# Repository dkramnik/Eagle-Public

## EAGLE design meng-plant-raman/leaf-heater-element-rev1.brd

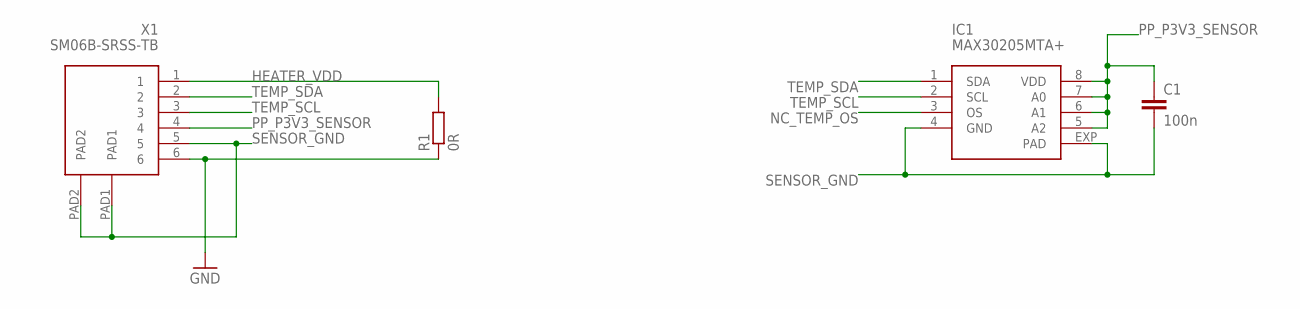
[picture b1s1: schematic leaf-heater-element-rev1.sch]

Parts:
C1: 100n; C0402
IC1: MAX30205MTA+; TDFN-08
R1: 0R; R0603
X1: SM06B-SRSS-TB; JST-SM06B-SRSS-TB

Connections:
GND: R1.1, X1.6
HEATER_VDD: R1.2, X1.1
NC_TEMP_OS: IC1.3 (OS)
PP_P3V3_SENSOR: C1.1, IC1.5 (A2), IC1.6 (A1), IC1.7 (A0), IC1.8 (VDD), X1.4
SENSOR_GND: C1.2, IC1.4 (GND), IC1.EXP (PAD), X1.5, X1.PAD1, X1.PAD2
TEMP_SCL: IC1.2 (SCL), X1.3
TEMP_SDA: IC1.1 (SDA), X1.2

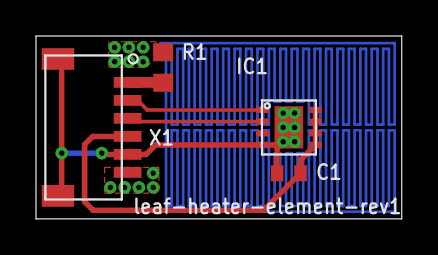
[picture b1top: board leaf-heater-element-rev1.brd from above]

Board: 2 copper layers, 20.3 x 10.2 mm, 4 parts (0 on the bottom side), 6 nets.

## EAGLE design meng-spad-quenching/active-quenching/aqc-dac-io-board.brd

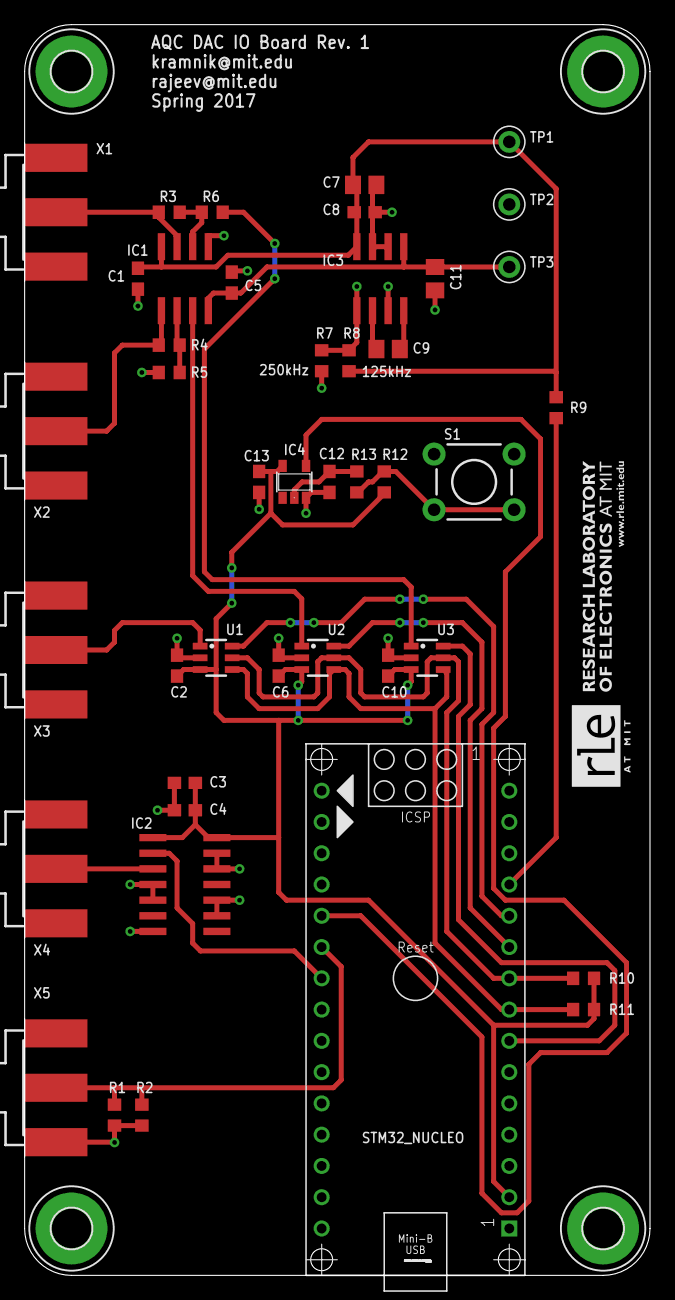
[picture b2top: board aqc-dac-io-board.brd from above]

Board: 2 copper layers, 50.8 x 101.6 mm, 47 parts (0 on the bottom side), 26 nets.

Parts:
C1, C2, C3, C5, C6, C8, C10, C12, C13: 100n; C0603
C4: 10n; C0603
C7, C9, C11: 4u7; C0805
H1, H2, H3, H4: MOUNT-PAD-ROUND3.2; 3,2-PAD
IC1: LT1366; SO08
IC2: 74LVT126; SO14
IC3: MAX1680; SO8
IC4: 74AHC1G14DBV; SOT23-5
R1, R2: 100R; R0603
R3: 15k0; R0603
R4: 5k11; R0603
R5, R6: 10k0; R0603
R7, R9: 0R; R0603
R8: DNP; R0603
R10, R11: 2k2; R0603
R12: 4k7; R0603
R13: 100k; R0603
S1: TACTILE-PTH
STM32_NUCLEO: ARDUINO_NANO
TP1: PP_P5V0; KEYSTONE_5000_MINIATURE
TP2: GND; KEYSTONE_5000_MINIATURE
TP3: PP_N5V0; KEYSTONE_5000_MINIATURE
U1, U2, U3: MCP4725; SOT23-6
X1: CONN_VREF_CASCODE_IBIAS; J502-ND-142-0701-801/806
X2: CONN_VREF_DIAMOND_IBIAS; J502-ND-142-0701-801/806
X3: CONN_VREF_ONE_SHOT; J502-ND-142-0701-801/806
X4: CONN_FORCE_QUENCH; J502-ND-142-0701-801/806
X5: CONN_PHOTON_COUNTER; J502-ND-142-0701-801/806

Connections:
DAC_CASCODE_IBIAS_SEL: STM32_NUCLEO.7, U3.6
DAC_DIAMOND_IBIAS_SEL: STM32_NUCLEO.10, U2.6
DAC_ONE_SHOT_SEL: STM32_NUCLEO.11, U1.6
DAC_SCL: R10.1, STM32_NUCLEO.9, U1.5, U2.5, U3.5
DAC_SDA: R11.1, STM32_NUCLEO.8, U1.4, U2.4, U3.4
FORCE_QUENCH_BUF: IC2.3, X4.1
FORCE_QUENCH_MCU: IC2.2, STM32_NUCLEO.22
GND: C1.2, C2.2, C3.2, C4.2, C5.2, C6.2, C7.2, C8.2, C10.2, C11.2, C12.2, C13.2, H1.B3,2, H2.B3,2, H3.B3,2, H4.B3,2, IC1.5, IC2.4, IC2.5, IC2.7, IC2.9, IC2.10, IC2.12, IC2.13, IC3.3, IC3.6, IC3.7, IC4.3, R1.1, R2.1, R5.1, R7.1, S1.1, S1.2, STM32_NUCLEO.14, STM32_NUCLEO.19, TP2.P$1, U1.2, U2.2, U3.2, X1.G@1, X1.G@2, X1.G@3, X1.G@4, X2.G@1, X2.G@2, X2.G@3, X2.G@4, X3.G@1, X3.G@2, X3.G@3, X3.G@4, X4.G@1, X4.G@2, X4.G@3, X4.G@4, X5.G@1, X5.G@2, X5.G@3, X5.G@4
unnamed: U1.1, X3.1
unnamed: R6.2, U3.1
unnamed: IC1.6, R3.2, R6.1
unnamed: IC3.1, R7.2, R8.1
unnamed: IC1.7, R3.1, X1.1
unnamed: IC1.3, U2.1
unnamed: IC1.1, R4.2, X2.1
unnamed: IC1.2, R4.1, R5.2
unnamed: R9.2, STM32_NUCLEO.12
unnamed: R12.1, R13.2, S1.3, S1.4
unnamed: C12.1, IC4.2, R13.1
unnamed: C9.2, IC3.4
unnamed: C9.1, IC3.2
PHOTON_COUNTER: R1.2, R2.2, STM32_NUCLEO.21, X5.1
PP_N5V0: C5.1, C11.1, IC1.4, IC3.5, TP3.P$1
PP_P3V3: C2.1, C3.1, C4.1, C6.1, C10.1, C13.1, IC2.1, IC2.14, IC4.5, R10.2, R11.2, R12.2, STM32_NUCLEO.2, U1.3, U2.3, U3.3
PP_P5V0: C1.1, C7.1, C8.1, IC1.8, IC3.8, R8.2, R9.1, TP1.P$1
TRIGGER_BTN: IC4.4, STM32_NUCLEO.20

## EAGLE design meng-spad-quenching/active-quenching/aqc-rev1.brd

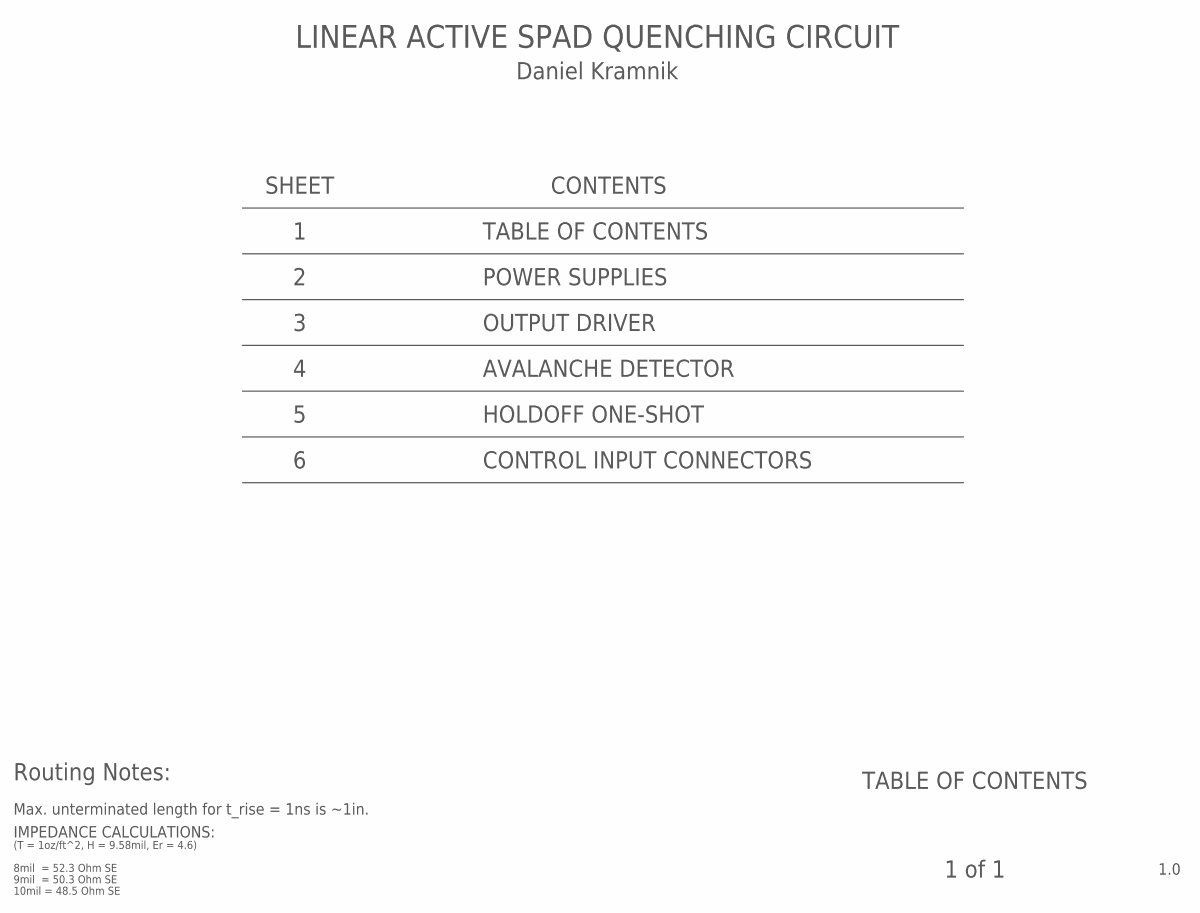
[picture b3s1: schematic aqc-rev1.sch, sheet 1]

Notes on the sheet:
IMPEDANCE CALCULATIONS:
(T = 1oz/ft^2, H = 9.58mil, Er = 4.6)
9mil = 50.3 Ohm SE
10mil = 48.5 Ohm SE
8mil = 52.3 Ohm SE
TABLE OF CONTENTS
1.0
1 of 1
LINEAR ACTIVE SPAD QUENCHING CIRCUIT
SHEET
CONTENTS
Daniel Kramnik
POWER SUPPLIES
OUTPUT DRIVER
AVALANCHE DETECTOR
HOLDOFF ONE-SHOT
CONTROL INPUT CONNECTORS
Routing Notes:
Max. unterminated length for t_rise = 1ns is ~1in.

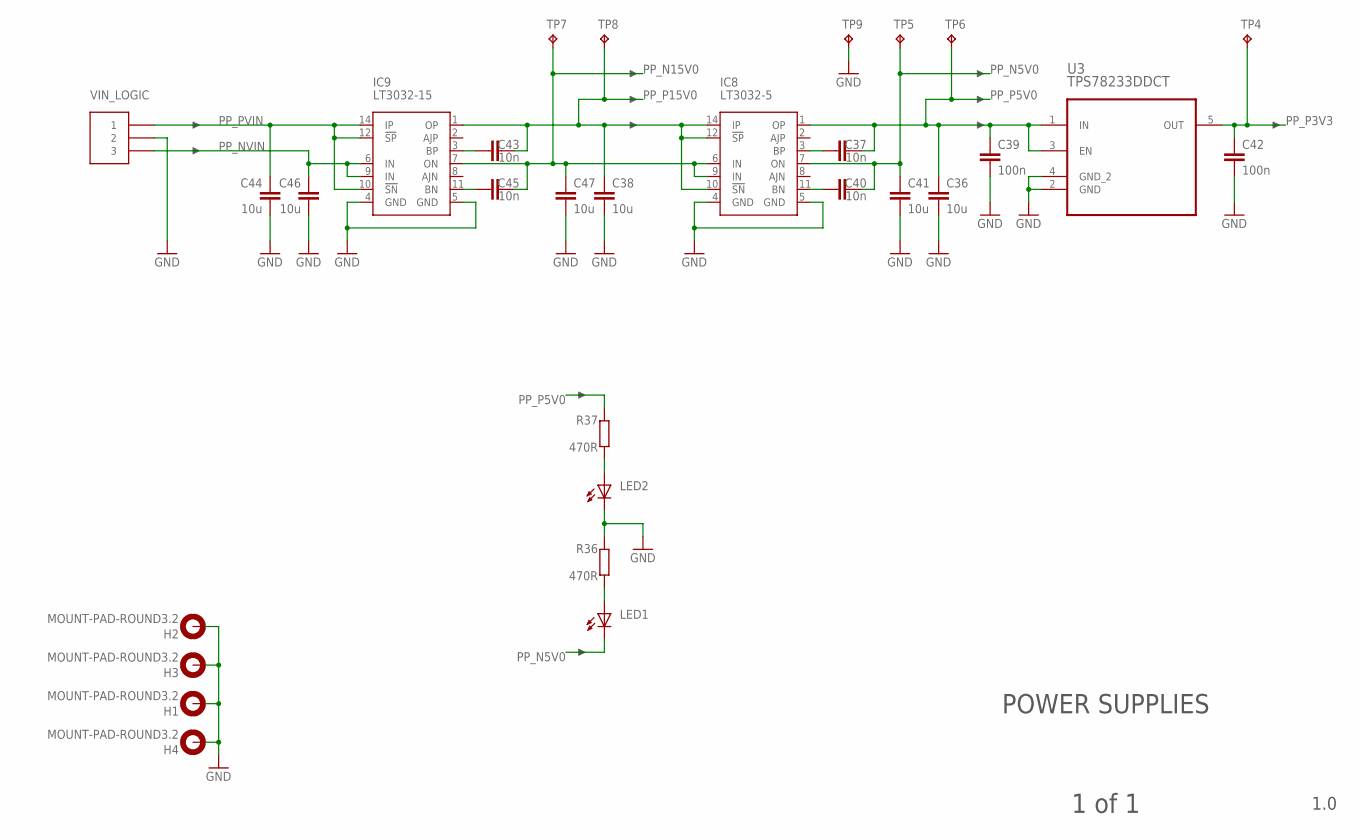
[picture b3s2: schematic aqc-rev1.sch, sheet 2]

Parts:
C36, C38, C41, C44, C46, C47: 10u; C1206
C37, C40, C43, C45: 10n; C0603
C39, C42: 100n; C0603
H1, H2, H3, H4: MOUNT-PAD-ROUND3.2; 3,2-PAD
IC8: LT3032-5; DFN14-4X3DE
IC9: LT3032-15; DFN14-4X3DE
J1: VIN_LOGIC; CONN_MOLEX_3PIN_MINI-FIT_JR
LED1, LED2: LEDCHIP-LED0805; CHIP-LED0805
R36, R37: 470R; R0805
TP4, TP5, TP6, TP7, TP8, TP9: TPTP20R; TP20R
U3: TPS78233DDCT; SOT95P280X110-5N

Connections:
GND: C36.2, C38.2, C39.2, C41.2, C42.2, C44.2, C46.2, C47.2, H1.B3,2, H2.B3,2, H3.B3,2, H4.B3,2, IC8.4 (GND), IC8.5 (GND), IC9.4 (GND), IC9.5 (GND), J1.2, LED2.C, R36.2, TP9.TP, U3.2 (GND), U3.4 (GND_2); also elsewhere on the board
unnamed: C37.1, IC8.3 (BP)
unnamed: C40.1, IC8.11 (BN)
unnamed: C43.1, IC9.3 (BP)
unnamed: C45.1, IC9.11 (BN)
unnamed: LED1.A, R36.1
unnamed: LED2.A, R37.1
PP_N5V0: C40.2, C41.1, IC8.7 (ON), LED1.C, TP5.TP; also elsewhere on the board
PP_N15V0: C45.2, C47.1, IC8.6 (IN), IC8.9 (IN), IC9.7 (ON), TP7.TP
PP_NVIN: C46.1, IC9.6 (IN), IC9.9 (IN), J1.3
PP_P3V3: C42.1, TP4.TP, U3.5 (OUT); also elsewhere on the board
PP_P5V0: C36.1, C37.2, C39.1, IC8.1 (OP), R37.2, TP6.TP, U3.1 (IN), U3.3 (EN); also elsewhere on the board
PP_P15V0: C38.1, C43.2, IC8.10 (!SN), IC8.12 (!SP), IC8.14 (IP), IC9.1 (OP), TP8.TP; also elsewhere on the board
PP_PVIN: C44.1, IC9.10 (!SN), IC9.12 (!SP), IC9.14 (IP), J1.1

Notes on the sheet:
POWER SUPPLIES
1.0
1 of 1

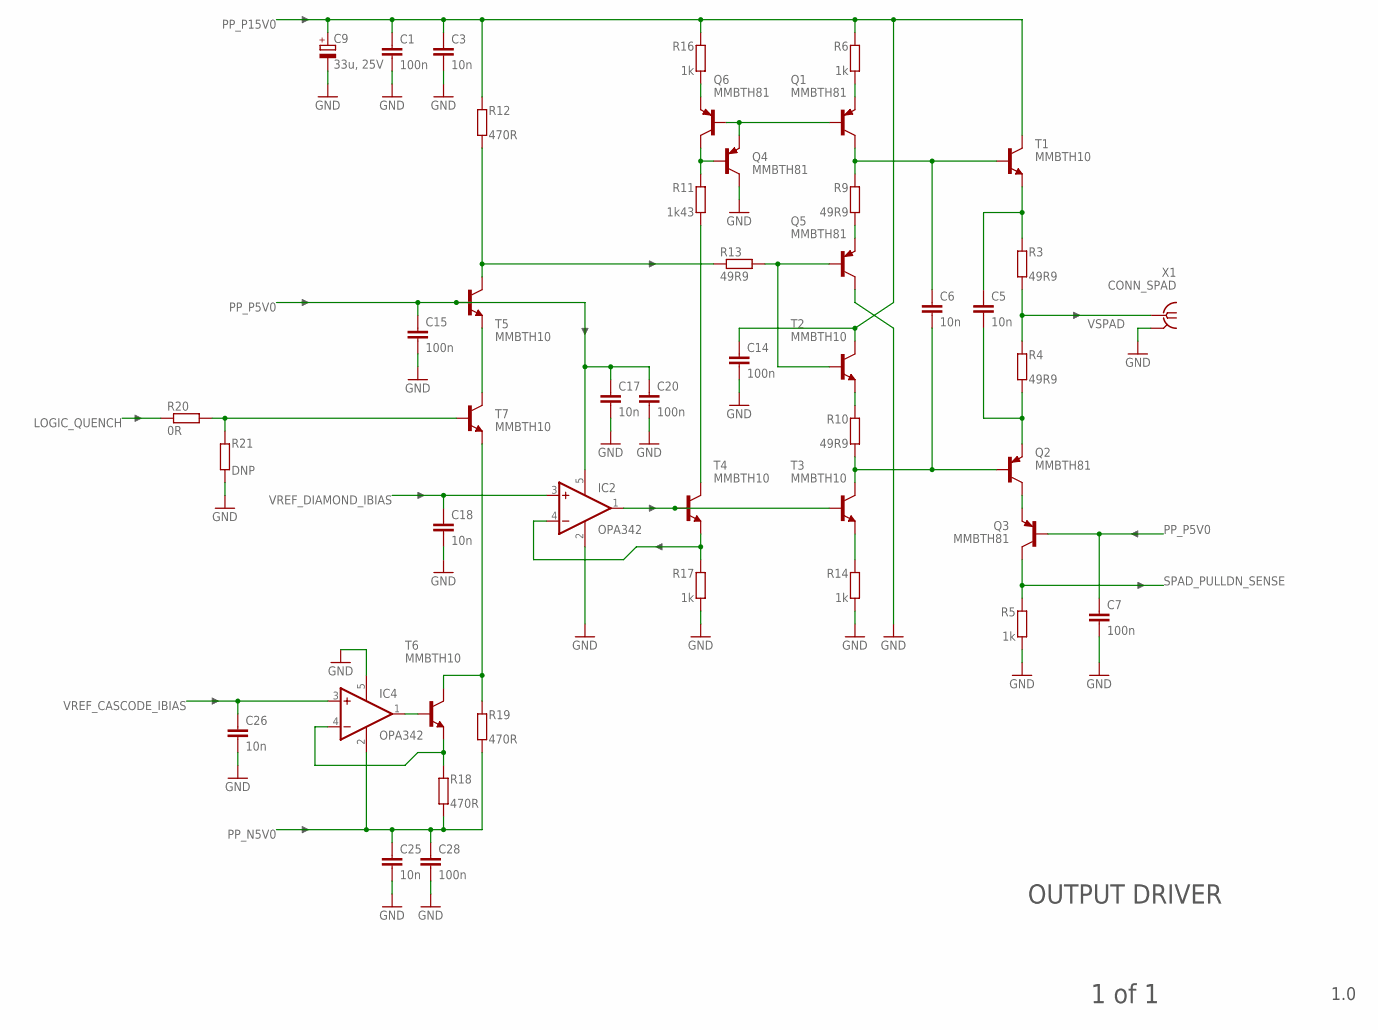
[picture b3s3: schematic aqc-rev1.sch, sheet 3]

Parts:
C1, C7, C14, C15: 100n; C0603
C3, C5, C6: 10n; C0603
C9: 33u, 25V; CT7343
C17, C18, C25, C26: 10n; C0402
C20, C28: 100n; C0402
IC2, IC4: OPA342; SOT23-5
Q1, Q2, Q3, Q4, Q5, Q6: MMBTH81; SOT23-BEC
R3, R4, R9, R10, R13: 49R9; R0603
R5, R6, R14, R16, R17: 1k; R0603
R11: 1k43; R0603
R12, R18, R19: 470R; R0603
R20: 0R; R0603
R21: DNP; R0603
T1, T2, T3, T4, T5, T6, T7: MMBTH10; SOT23-BEC
X1: CONN_SPAD; J502-ND-142-0711-871/876

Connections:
GND: C1.2, C3.2, C7.2, C9.-, C14.2, C15.2, C17.2, C18.2, C20.2, C25.2, C26.2, C28.2, IC2.2 (V-), IC4.5 (V+), Q4.C, Q5.C, R5.1, R14.1, R17.1, R21.2, X1.G@1 (GND), X1.G@2 (GND), X1.G@3 (GND), X1.G@4 (GND); also elsewhere on the board
LOGIC_QUENCH: R20.2; also elsewhere on the board
LOGIC_QUENCH_ATTEN: R20.1, R21.1, T7.B
unnamed: C5.1, R3.2, T1.E
unnamed: Q2.C, Q3.E
unnamed: Q5.E, R9.1
unnamed: C6.1, Q1.C, R9.2, T1.B
unnamed: R10.2, T2.E
unnamed: C5.2, Q2.E, R4.1
unnamed: T5.E, T7.C
unnamed: IC2.1 (OUT), T3.B, T4.B
unnamed: Q4.B, Q6.C, R11.2
unnamed: C6.2, Q2.B, R10.1, T3.C
unnamed: R14.2, T3.E
unnamed: Q5.B, R13.1, T2.B
unnamed: R12.1, R13.2, T5.C
unnamed: IC2.4 (-IN), R17.2, T4.E
unnamed: R19.2, T6.C, T7.E
unnamed: Q1.E, R6.1
unnamed: R11.1, T4.C
unnamed: Q6.E, R16.1
unnamed: IC4.1 (OUT), T6.B
unnamed: Q1.B, Q4.E, Q6.B
unnamed: IC4.4 (-IN), R18.2, T6.E
PP_N5V0: C25.1, C28.1, IC4.2 (V-), R18.1, R19.1; also elsewhere on the board
PP_P5V0: C7.1, C15.1, C17.1, C20.1, IC2.5 (V+), Q3.B, T5.B; also elsewhere on the board
PP_P15V0: C1.1, C3.1, C9.+, C14.1, R6.2, R12.2, R16.2, T1.C, T2.C; also elsewhere on the board
SPAD_PULLDN_SENSE: Q3.C, R5.2; also elsewhere on the board
VREF_CASCODE_IBIAS: C26.1, IC4.3 (+IN); also elsewhere on the board
VREF_DIAMOND_IBIAS: C18.1, IC2.3 (+IN); also elsewhere on the board
VSPAD: R3.1, R4.2, X1.1

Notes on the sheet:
OUTPUT DRIVER
1.0
1 of 1

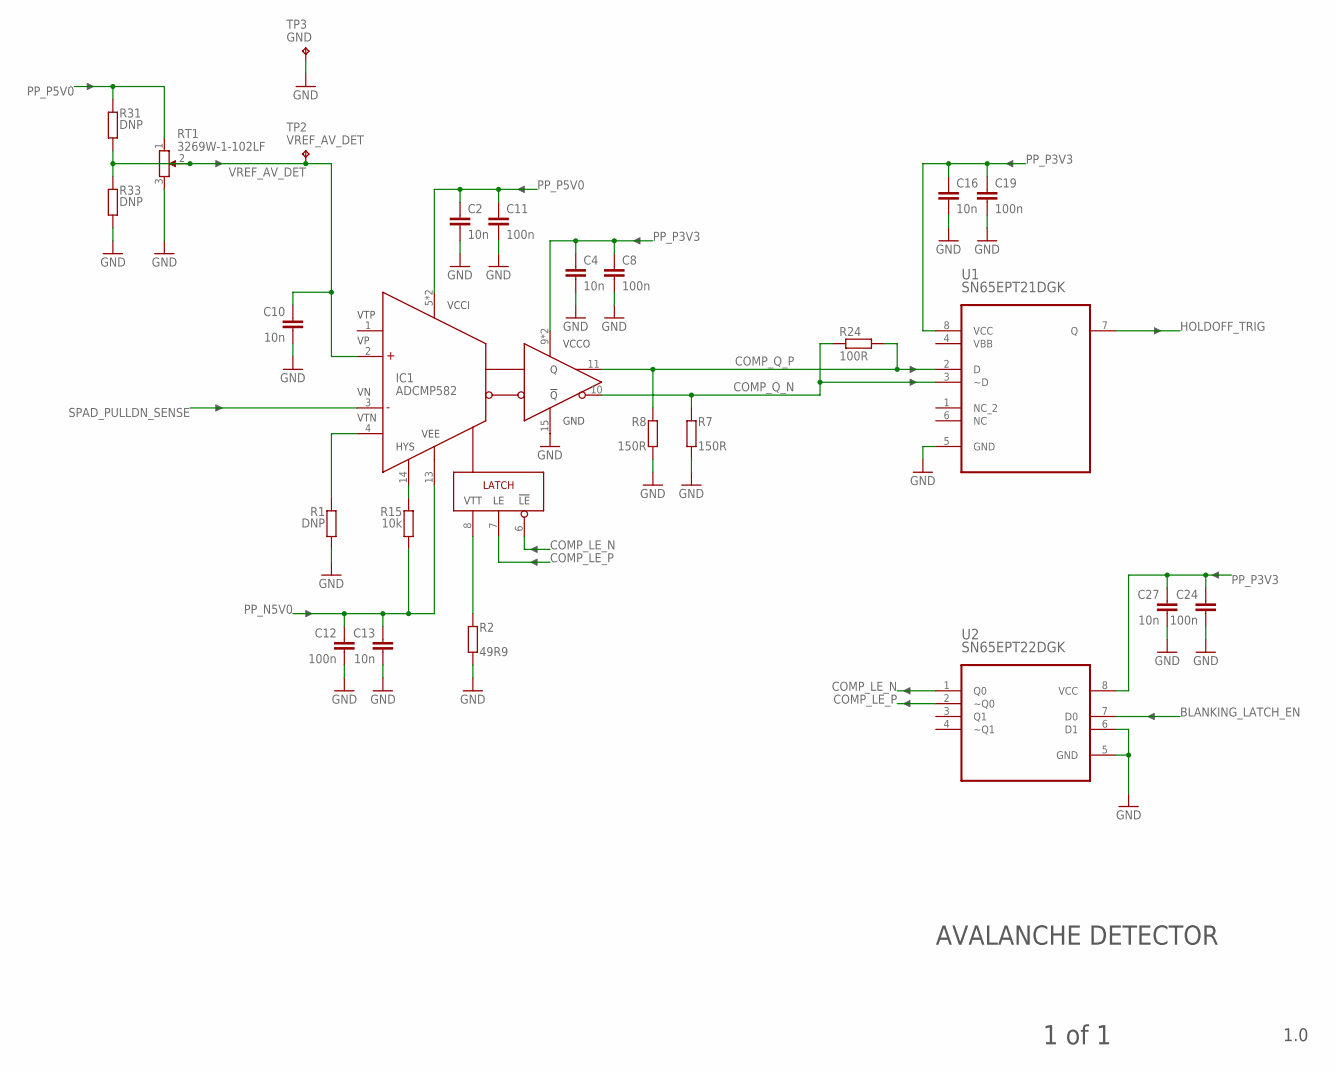
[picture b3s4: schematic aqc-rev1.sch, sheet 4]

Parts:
C2, C4, C13, C16, C27: 10n; C0402
C8, C11, C12, C19, C24: 100n; C0402
C10: 10n; C0603
IC1: ADCMP582; QFN50P300X300X80-16N
R1, R31, R33: DNP; R0603
R2: 49R9; R0603
R7, R8: 150R; R0402
R15: 10k; R0603
R24: 100R; R0402
RT1: 3269W-1-102LF; 3269W
TP2: VREF_AV_DET; KEYSTONE_5000_MINIATURE
TP3: GND; KEYSTONE_5000_MINIATURE
U1: SN65EPT21DGK; SOP65P490X110-8N
U2: SN65EPT22DGK; SOP65P490X110-8N

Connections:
BLANKING_LATCH_EN: U2.7 (D0); also elsewhere on the board
COMP_LE_N: IC1.6 (!LE), U2.1 (Q0)
COMP_LE_P: IC1.7 (LE), U2.2 (~Q0)
COMP_Q_N: IC1.10 (!Q), R7.1, R24.1, U1.3 (~D)
COMP_Q_P: IC1.11 (Q), R8.1, R24.2, U1.2 (D)
GND: C2.2, C4.2, C8.2, C10.2, C11.2, C12.2, C13.2, C16.2, C19.2, C24.2, C27.2, IC1.15 (GND), R1.1, R2.2, R7.2, R8.2, R33.1, RT1.3, TP3.P$1, U1.5 (GND), U2.5 (GND), U2.6 (D1); also elsewhere on the board
HOLDOFF_TRIG: U1.7 (Q); also elsewhere on the board
unnamed: IC1.4 (VTN), R1.2
unnamed: IC1.14 (HYS), R15.2
unnamed: IC1.8 (VTT), R2.1
PP_N5V0: C12.1, C13.1, IC1.13 (VEE), R15.1; also elsewhere on the board
PP_P3V3: C4.1, C8.1, C16.1, C19.1, C24.1, C27.1, IC1.9 (VCCO), IC1.12 (VCCO), U1.8 (VCC), U2.8 (VCC); also elsewhere on the board
PP_P5V0: C2.1, C11.1, IC1.5 (VCCI), IC1.16 (VCCI), R31.2, RT1.1; also elsewhere on the board
SPAD_PULLDN_SENSE: IC1.3 (VN); also elsewhere on the board
VBB: U1.4 (VBB)
VREF_AV_DET: C10.1, IC1.2 (VP), R31.1, R33.2, RT1.2, TP2.P$1

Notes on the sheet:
AVALANCHE DETECTOR
1.0
1 of 1

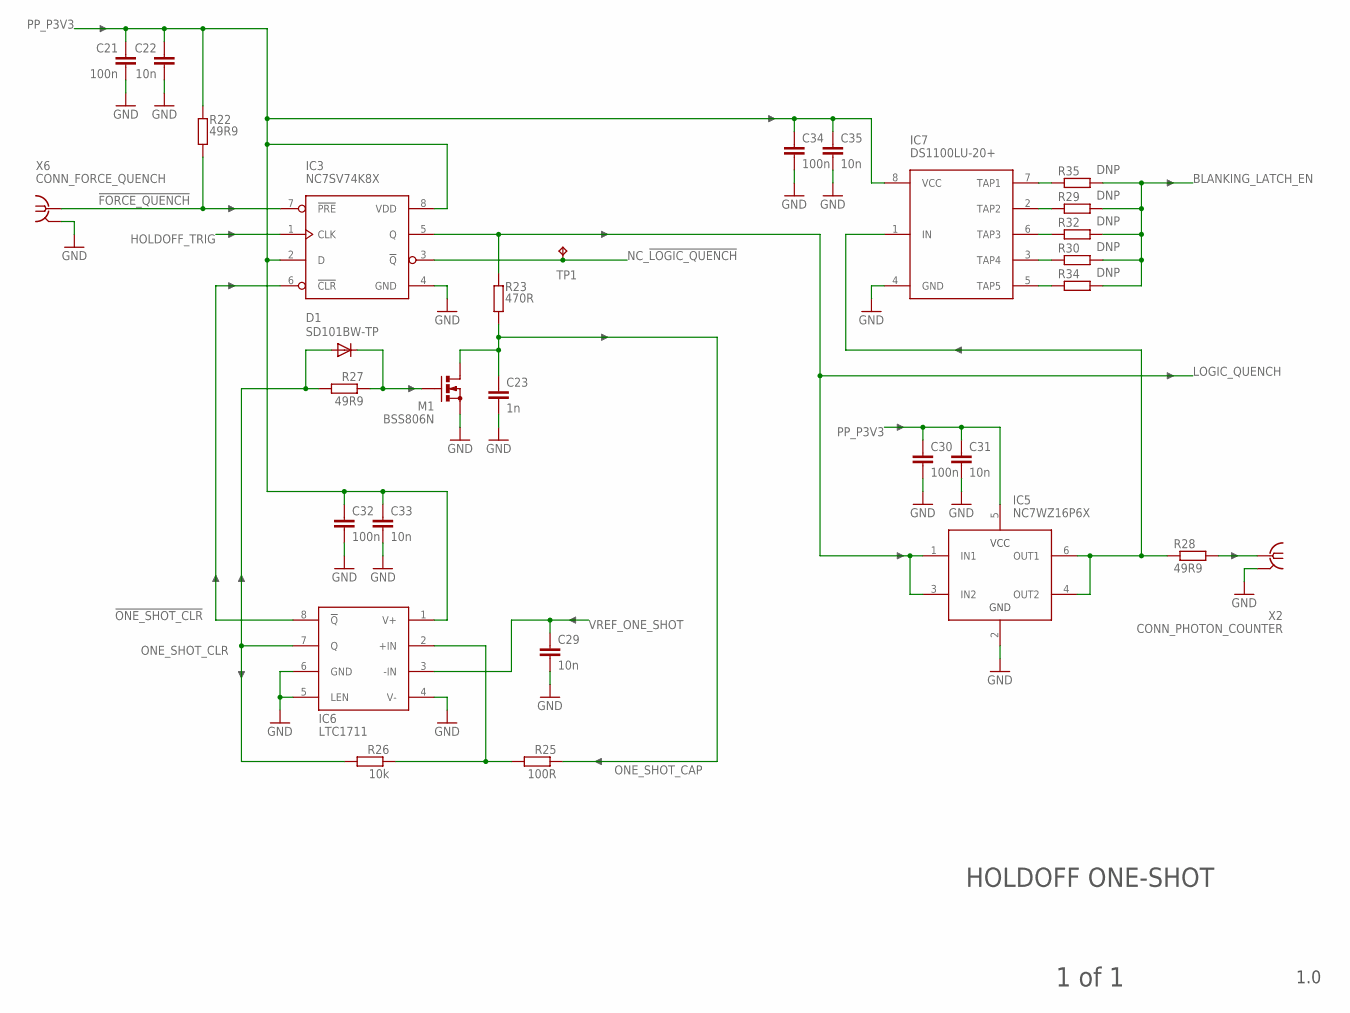
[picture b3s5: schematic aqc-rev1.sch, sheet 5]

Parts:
C21, C30, C32, C34: 100n; C0402
C22, C29, C31, C33, C35: 10n; C0402
C23: 1n; C0603
D1: SD101BW-TP; SOD123
IC3: NC7SV74K8X; US8_3.1MM_JDEC_MO-187
IC5: NC7WZ16P6X; SC70-6L
IC6: LTC1711; MSOP8
IC7: DS1100LU-20+; MSOP8
M1: BSS806N; SOT23R_INFINEON
R22, R27, R28: 49R9; R0603
R23: 470R; R0603
R25: 100R; R0603
R26: 10k; R0603
R29, R30, R32, R34, R35: DNP; R0603
TP1: TPTP08R; TP08R
X2: CONN_PHOTON_COUNTER; J502-ND-142-0711-871/876
X6: CONN_FORCE_QUENCH; J502-ND-142-0711-871/876; MPN 142-0711-871

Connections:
!FORCE_QUENCH: IC3.7 (!PRE), R22.1, X6.1
!ONE_SHOT_CLR: IC3.6 (!CLR), IC6.8 (!Q)
BLANKING_LATCH_EN: R29.1, R30.1, R32.1, R34.1, R35.1; also elsewhere on the board
GND: C21.2, C22.2, C23.2, C29.2, C30.2, C31.2, C32.2, C33.2, C34.2, C35.2, IC3.4 (GND), IC5.2 (GND), IC6.4 (V-), IC6.5 (LEN), IC6.6 (GND), IC7.4 (GND), M1.2 (S), X2.G@1 (GND), X2.G@2 (GND), X2.G@3 (GND), X2.G@4 (GND), X6.G@1 (GND), X6.G@2 (GND), X6.G@3 (GND), X6.G@4 (GND); also elsewhere on the board
HOLDOFF_TRIG: IC3.1 (CLK); also elsewhere on the board
LOGIC_QUENCH: IC3.5 (Q), IC5.1 (IN1), IC5.3 (IN2), R23.2; also elsewhere on the board
unnamed: R28.1, X2.1
unnamed: IC6.2 (+IN), R25.1, R26.2
unnamed: D1.C, M1.1 (G), R27.2
unnamed: IC5.4 (OUT2), IC5.6 (OUT1), IC7.1 (IN), R28.2
NC_!LOGIC_QUENCH: IC3.3 (!Q), TP1.TP
ONE_SHOT_CAP: C23.1, M1.3 (D), R23.1, R25.2
ONE_SHOT_CLR: D1.A, IC6.7 (Q), R26.1, R27.1
PP_P3V3: C21.1, C22.1, C30.1, C31.1, C32.1, C33.1, C34.1, C35.1, IC3.2 (D), IC3.8 (VDD), IC5.5 (VCC), IC6.1 (V+), IC7.8 (VCC), R22.2; also elsewhere on the board
TAP1: IC7.7 (TAP1), R35.2
TAP2: IC7.2 (TAP2), R29.2
TAP3: IC7.6 (TAP3), R32.2
TAP4: IC7.3 (TAP4), R30.2
TAP5: IC7.5 (TAP5), R34.2
VREF_ONE_SHOT: C29.1, IC6.3 (-IN); also elsewhere on the board

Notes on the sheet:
HOLDOFF ONE-SHOT
1.0
1 of 1

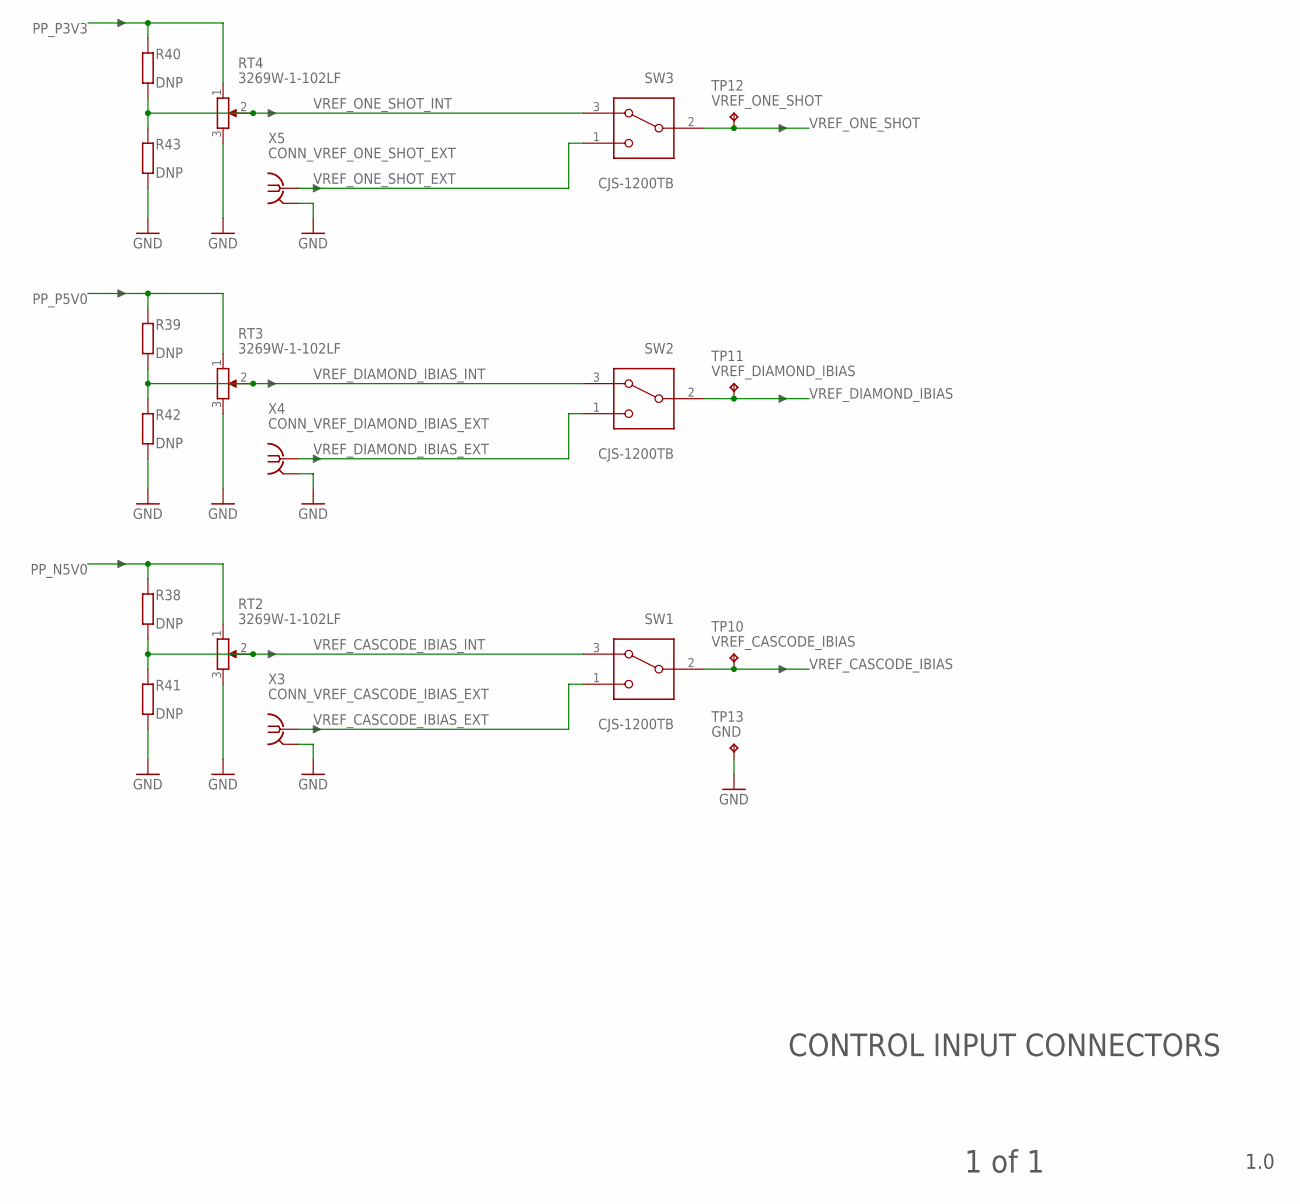
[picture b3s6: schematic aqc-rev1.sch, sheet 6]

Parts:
R38, R39, R40, R41, R42, R43: DNP; R0603
RT2, RT3, RT4: 3269W-1-102LF; 3269W
SW1, SW2, SW3: CJS-1200TB
TP10: VREF_CASCODE_IBIAS; KEYSTONE_5000_MINIATURE
TP11: VREF_DIAMOND_IBIAS; KEYSTONE_5000_MINIATURE
TP12: VREF_ONE_SHOT; KEYSTONE_5000_MINIATURE
TP13: GND; KEYSTONE_5000_MINIATURE
X3: CONN_VREF_CASCODE_IBIAS_EXT; J502-ND-142-0711-871/876
X4: CONN_VREF_DIAMOND_IBIAS_EXT; J502-ND-142-0711-871/876
X5: CONN_VREF_ONE_SHOT_EXT; J502-ND-142-0711-871/876

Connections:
GND: R41.2, R42.2, R43.2, RT2.3, RT3.3, RT4.3, TP13.P$1, X3.G@1 (GND), X3.G@2 (GND), X3.G@3 (GND), X3.G@4 (GND), X4.G@1 (GND), X4.G@2 (GND), X4.G@3 (GND), X4.G@4 (GND), X5.G@1 (GND), X5.G@2 (GND), X5.G@3 (GND), X5.G@4 (GND); also elsewhere on the board
PP_N5V0: R38.1, RT2.1; also elsewhere on the board
PP_P3V3: R40.1, RT4.1; also elsewhere on the board
PP_P5V0: R39.1, RT3.1; also elsewhere on the board
VREF_CASCODE_IBIAS: SW1.2 (COM), TP10.P$1; also elsewhere on the board
VREF_CASCODE_IBIAS_EXT: SW1.1 (NO), X3.1
VREF_CASCODE_IBIAS_INT: R38.2, R41.1, RT2.2, SW1.3 (NC)
VREF_DIAMOND_IBIAS: SW2.2 (COM), TP11.P$1; also elsewhere on the board
VREF_DIAMOND_IBIAS_EXT: SW2.1 (NO), X4.1
VREF_DIAMOND_IBIAS_INT: R39.2, R42.1, RT3.2, SW2.3 (NC)
VREF_ONE_SHOT: SW3.2 (COM), TP12.P$1; also elsewhere on the board
VREF_ONE_SHOT_EXT: SW3.1 (NO), X5.1
VREF_ONE_SHOT_INT: R40.2, R43.1, RT4.2, SW3.3 (NC)

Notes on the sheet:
CONTROL INPUT CONNECTORS
1.0
1 of 1

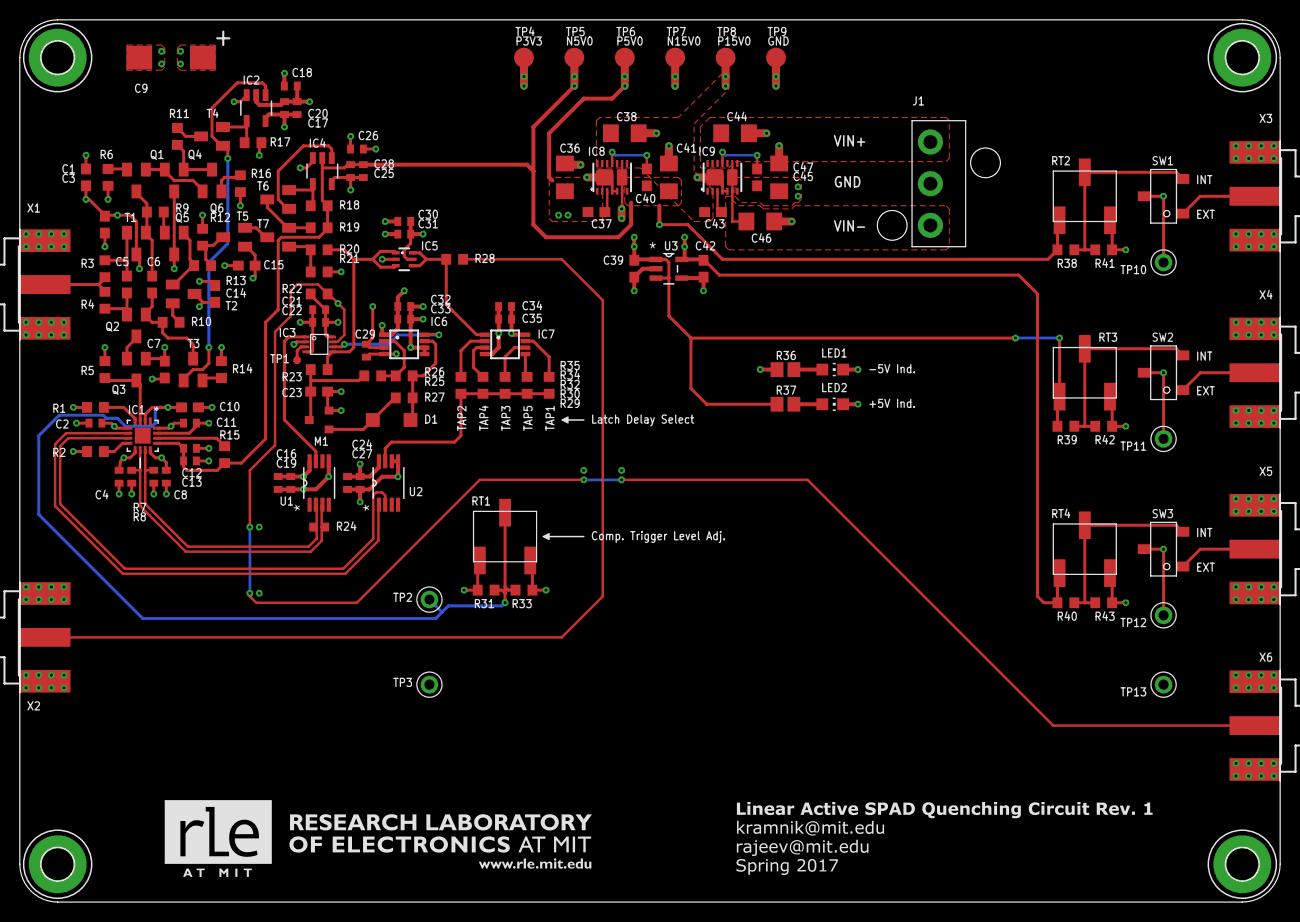
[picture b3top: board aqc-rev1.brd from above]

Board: 4 copper layers, 127.0 x 88.9 mm, 150 parts (0 on the bottom side), 72 nets.

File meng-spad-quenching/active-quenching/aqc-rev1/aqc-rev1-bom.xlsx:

| aqc-rev1 BOM
 | Note: Cost is with MIT negotiated price, bulk discount not included.
BOM # | Part | Value | Rating | Package | Description | Digikey P/N | Cost/Unit | Qty. | Cost/Qty.
1 | C1, C7, C14, C15, C39, C42 | 100n | 25V | C0603 | CAP CER 0.1UF 25V X7R 0603 | 490-1524-1-ND | 0.09 | 6 | 0.54
2 | C2, C4, C13, C16, C17, C18, C22, C25, C26, C27, C29, C31, C33, C35 | 10n | 25V | C0402 | CAP CER 10000PF 25V X7R 0402 | 490-1312-1-ND | 0.09 | 14 | 1.26
3 | C3, C5, C6, C10, C37, C40, C43, C45 | 10n | 25V | C0603 | CAP CER 10000PF 25V X7R 0603 | 1276-1132-1-ND | 0.09 | 8 | 0.72
4 | C8, C11, C12, C19, C20, C21, C24, C28, C30, C32, C34 | 100n | 25V | C0402 | CAP CER 0.1UF 25V X7R 0402 | 490-10698-1-ND | 0.09 | 11 | 0.99
5 | C9 | 33u | 25V | C7343 | CAP ALUM POLY 33UF 20% 25V SMD | P16819-1-ND | 1.45 | 1 | 1.45
6 | C23 | 1n | 16V | C0603 | CAP FILM 1000PF 2% 16VDC 0603 | PCF1453CT-ND | 0.38 | 1 | 0.38
7 | C36, C38, C41, C44, C46, C47 | 10u | 25V | C1206 | CAP CER 10UF 25V X7R 1206 | 490-6518-1-ND | 0.22 | 6 | 1.32
8 | D1 | SD101BW-TP | 50V | SOD123 | DIODE SCHOTTKY 50V 15MA SOD123 | SD101BWTPMSCT-ND | 0.3 | 1 | 0.3
9 | IC1 | ADCMP582 |  | 16LFCSP | IC COMPARATOR PECL UFAST 16LFCSP | ADCMP582BCPZ-WP | 15.89 | 1 | 15.89
10 | IC2, IC4 | OPA342 |  | SOT23-5 | IC OPAMP GP 1MHZ RRO SOT23-5 | 296-41474-1-ND | 0.97 | 2 | 1.94
11 | IC3 | NC7SV74K8X |  | US8 | IC D-TYPE POS TRG SNGL US8 | NC7SV74K8XCT-ND | 0.51 | 1 | 0.51
12 | IC5 | NC7WZ16P6X |  | SC70-6L | IC BUFFER DL UHS N-INV SC70-6 | NC7WZ16P6XCT-ND | 0.34 | 1 | 0.34
13 | IC6 | LTC1711 |  | MSOP8 | IC COMP R-RINOUT SINGLE 8-MSOP | LT1711CMS8#PBF-ND | 4.4000000000000004 | 1 | 4.4000000000000004
14 | IC7 | DS1100LU-20+ |  | MSOP8 | IC DELAY LINE 5TAP 20NS 8UMAX | DS1100LU-20+-ND | 5.14 | 1 | 5.14
15 | IC8 | LT3032-5 |  | 14DFN | IC REG LDO +-5V 0.15A 14DFN | LT3032EDE-5#PBF-ND | 4.7 | 1 | 4.7
16 | IC9 | LT3032-15 |  | 14DFN | IC REG LDO +-15V 0.15A 14DFN | LT3032EDE-15#PBF-ND | 4.7 | 1 | 4.7
17 | J1 | VIN_LOGIC |  | Custom | CONN HEADER 3POS SNGL VERT GOLD | WM7251-ND | 1.2 | 1 | 1.2
18 | LED1, LED2 | LEDCHIP-LED0805 |  | LED0805 | LED GREEN CLEAR 0805 SMD | 732-4986-1-ND | 0.28999999999999998 | 2 | 0.57999999999999996
19 | M1 | BSS806N | 20V | SOT23R | MOSFET N-CH 20V 2.3A SOT23 | BSS806N H6327CT-ND | 0.3 | 1 | 0.3
20 | Q1, Q2, Q3, Q4, Q5, Q6 | MMBTH81 |  | SOT23-BEC | TRANSISTOR RF PNP SOT-23 | MMBTH81CT-ND | 0.19 | 6 | 1.1400000000000001
DNP | R1, R21, R29, R30, R31, R32, R33, R34, R35, R38, R39, R40, R41, R42, R43 | DNP |  | R0603 | DNP, Buy Extra 0R Jumpers | N/A | 0 | 15 | 0
21 | R2, R3, R4, R9, R10, R13, R22, R27, R28 | 49R9 | 1/8W | R0603 | RES SMD 49.9 OHM 1% 1/8W 0603 | RNCP0603FTD49R9CT-ND | 0.09 | 9 | 0.80999999999999994
22 | R5, R6, R14, R16, R17 | 1k | 1/8W | R0603 | RES SMD 1K OHM 1% 1/8W 0603 | RNCP0603FTD1K00CT-ND | 0.09 | 5 | 0.44999999999999996
23 | R7, R8 | 150R | 1/10W | R0402 | RES SMD 150 OHM 1% 1/10W 0402 | P150LCT-ND | 0.09 | 2 | 0.18
24 | R11 | 1k43 | 1/10W | R0603 | RES SMD 1.43K OHM 1% 1/10W 0603 | 311-1.43KHRCT-ND | 0.09 | 1 | 0.09
25 | R12, R18, R19, R23 | 470R | 1/10W | R0603 | RES SMD 470 OHM 1% 1/10W 0603 | RMCF0603FT470RCT-ND | 0.09 | 4 | 0.36
26 | R15, R26 | 10k | 1/10W | R0603 | RES SMD 10K OHM 1% 1/10W 0603 | RMCF0603FT10K0CT-ND | 0.09 | 2 | 0.18
27 | R20 | 0R | 1/10W | R0603 | RES SMD 0.0OHM JUMPER 1/10W 0603 | 311-0.0GRCT-ND | 0.09 | 1 | 0.09
28 | R24, R25 | 100R | 1/10W | R0402 | RES SMD 100 OHM 1% 1/10W 0402 | P100LCT-ND | 0.09 | 2 | 0.18
29 | R36, R37 | 150R | 1/8W | R0805 | RES SMD 150 OHM 1% 1/8W 0805 | 311-150CRCT-ND | 0.09 | 2 | 0.18
30 | RT1, RT2, RT3, RT4 | 3269W-1-102LF | 0.25W | 3269W | TRIMMER 1K OHM 0.25W SMD | 3269W-1-102LF-ND | 4.1100000000000003 | 4 | 16.440000000000001
31 | SW1, SW2, SW3 | CJS-1200TB | 6V | CJS-1200TB | SWITCH SLIDE DIP SPDT 100MA 6V | 563-1022-1-ND | 0.73 | 3 | 2.19
32 | T1, T2, T3, T4, T5, T6, T7 | MMBTH10 | 25V | SOT23-BEC | TRANS VHF/UHF NPN 25V SOT-23 | MMBTH10-4LT1GOSCT-ND | 0.23 | 7 | 1.61
33 | TP2, TP10, TP11, TP12. TP13 | White TP VREF |  | Custom | TEST POINT PC MINI .040"D WHITE | 36-5002-ND | 0.32 | 5 | 1.6
34 | TP3, TP13 | Black TP GND |  | Custom | TEST POINT PC MINI .040"D BLACK | 36-5001-ND | 0.32 | 2 | 0.64
35 | U1 | SN65EPT21DGK |  | 8VSSOP | IC XLATR DIFF PECL/LVDS 8VSSOP | 296-27264-5-ND | 3.4 | 1 | 3.4
36 | U2 | SN65EPT22DGK |  | 8VSSOP | BUFFER DUAL LVPECL 3.3V 8VSSOP | 296-24086-5-ND | 3.4 | 1 | 3.4
37 | U3 | TPS78233DDCT |  | 5SOT | IC REG LDO 3.3V 0.15A 5SOT | 296-24120-1-ND | 0.74 | 1 | 0.74
38 | X1, X2, X3, X4, X5, X6 | CONN SMA |  | SMA-SMT | CONN SMA JACK 50 OHM EDGE MNT | WM5534-ND | 2.84 | 6 | 17.04
 |  |  |  |  |  |  | TOTAL: |  | 97.380000000000024

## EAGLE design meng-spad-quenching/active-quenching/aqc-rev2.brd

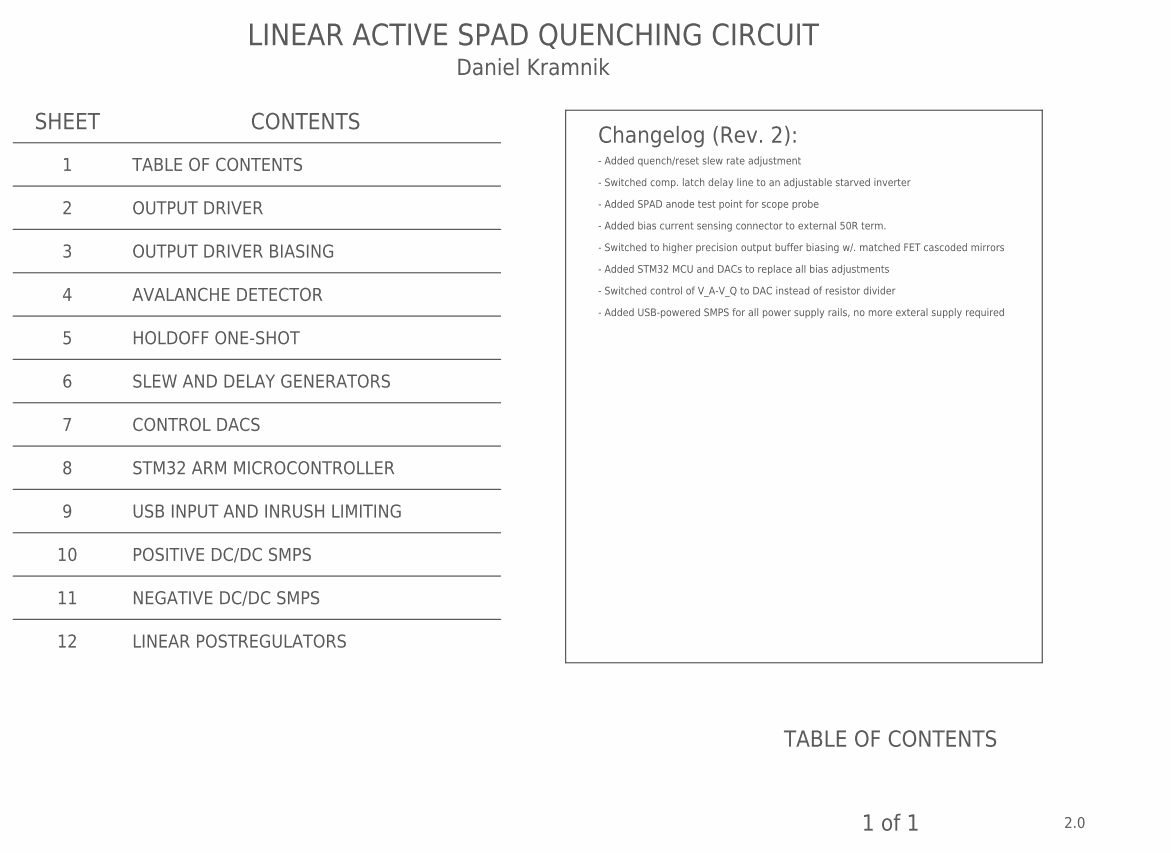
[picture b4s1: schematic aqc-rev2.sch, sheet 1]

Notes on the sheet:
Changelog (Rev. 2):
- Added quench/reset slew rate adjustment
- Switched comp. latch delay line to an adjustable starved inverter
- Added SPAD anode test point for scope probe
- Added bias current sensing connector to external 50R term.
- Added USB-powered SMPS for all power supply rails, no more exteral supply required
- Added STM32 MCU and DACs to replace all bias adjustments
- Switched to higher precision output buffer biasing w/. matched FET cascoded mirrors
- Switched control of V_A-V_Q to DAC instead of resistor divider
TABLE OF CONTENTS
2.0
1 of 1
LINEAR ACTIVE SPAD QUENCHING CIRCUIT
SHEET
CONTENTS
Daniel Kramnik
OUTPUT DRIVER
OUTPUT DRIVER BIASING
STM32 ARM MICROCONTROLLER
CONTROL DACS
AVALANCHE DETECTOR
POSITIVE DC/DC SMPS
NEGATIVE DC/DC SMPS
USB INPUT AND INRUSH LIMITING
HOLDOFF ONE-SHOT
SLEW AND DELAY GENERATORS
LINEAR POSTREGULATORS

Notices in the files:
parts and their libraries:
microbuilder: This work is placed in the public domain, and may be freely used for commercial and non-commercial work with the following conditions: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
SparkFun-Connectors: Licensing: Creative Commons ShareAlike 4.0 International - https://creativecommons.org/licenses/by-sa/4.0
